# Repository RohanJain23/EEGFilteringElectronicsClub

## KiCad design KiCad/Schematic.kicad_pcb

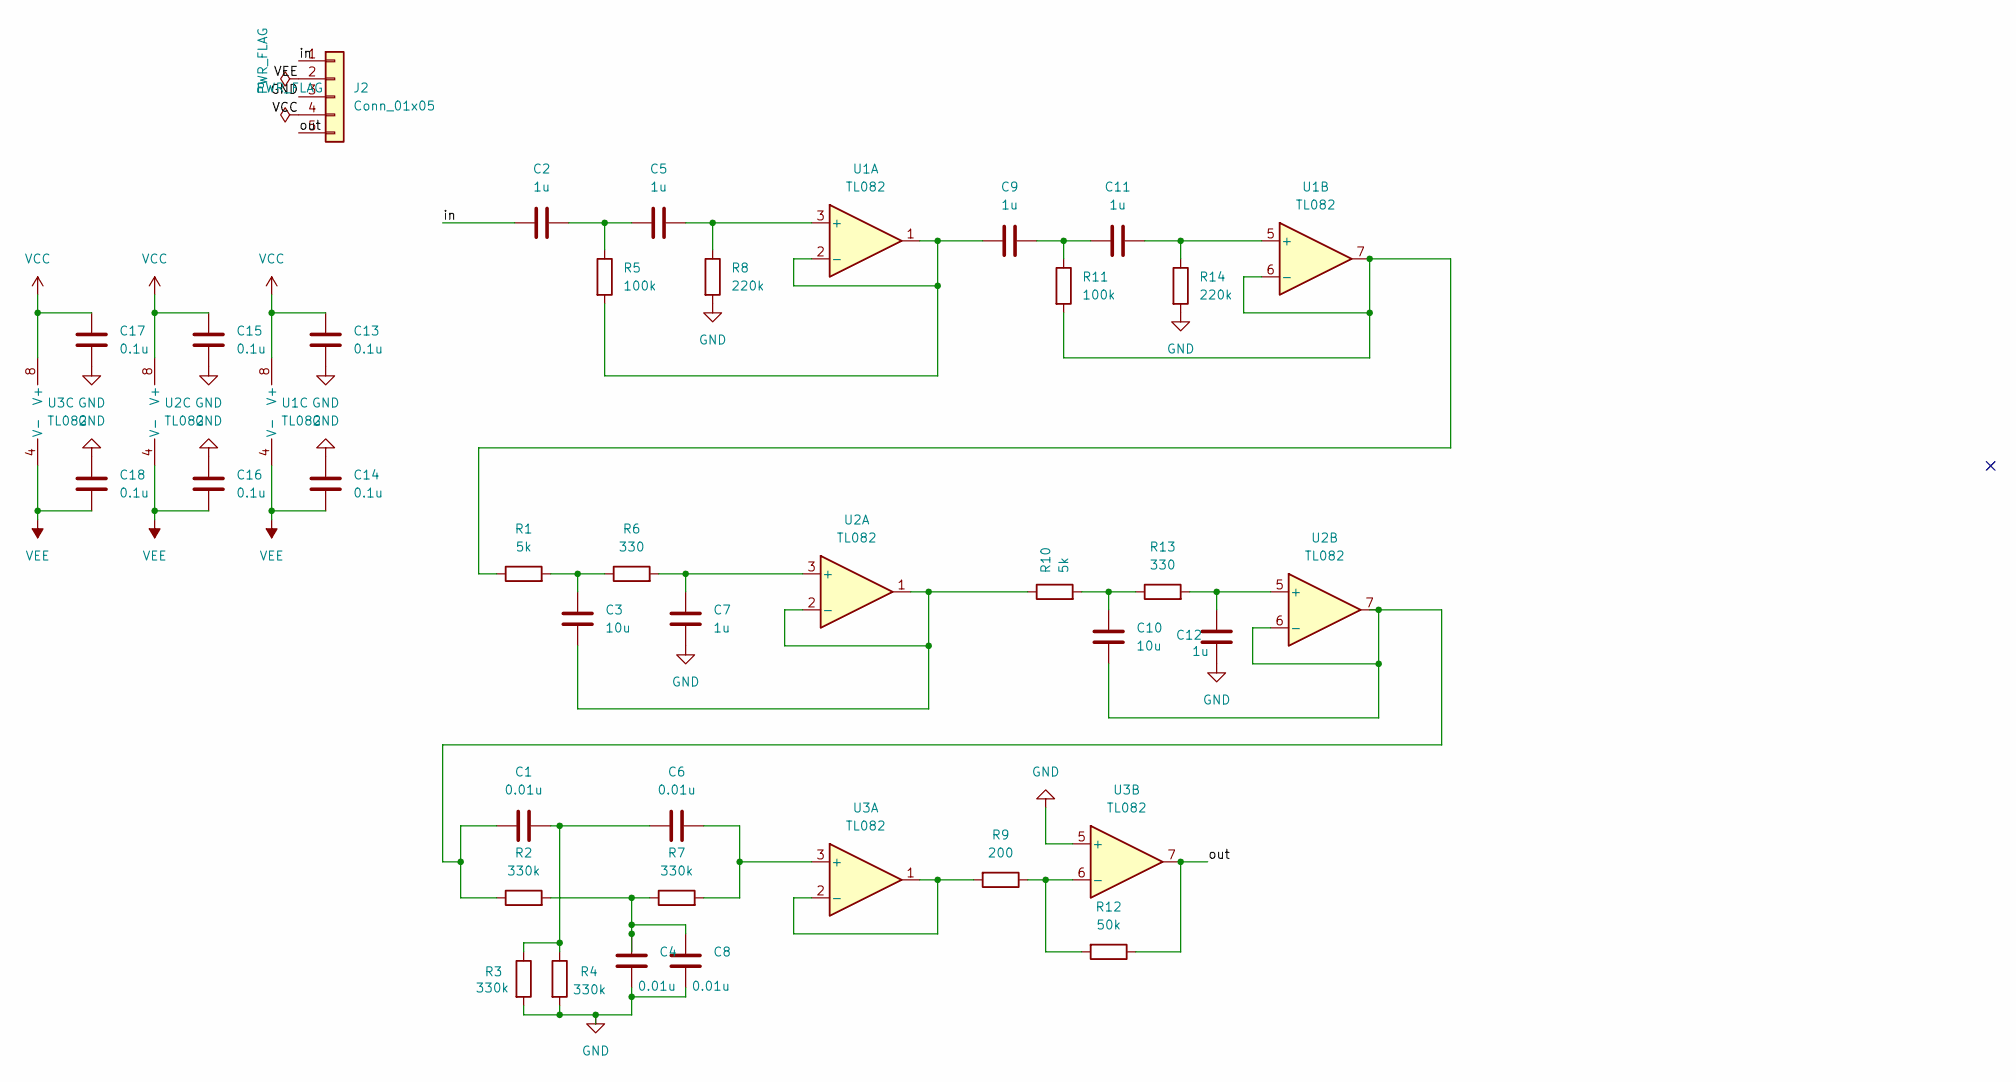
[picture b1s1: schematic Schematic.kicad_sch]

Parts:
C1, C4, C6, C8: 0.01u; C_Disc_D5.0mm_W2.5mm_P5.00mm
C2, C5, C7, C9, C11, C12: 1u; CP_Radial_D5.0mm_P2.50mm
C3, C10: 10u; CP_Radial_D5.0mm_P2.50mm
C13, C14, C15, C16, C17, C18: 0.1u; C_Disc_D5.0mm_W2.5mm_P5.00mm
J2: Conn_01x05; PinHeader_1x05_P2.54mm_Vertical
R1, R10: 5k; R_Axial_DIN0207_L6.3mm_D2.5mm_P7.62mm_Horizontal
R2, R3, R4, R7: 330k; R_Axial_DIN0207_L6.3mm_D2.5mm_P7.62mm_Horizontal
R5, R11: 100k; R_Axial_DIN0207_L6.3mm_D2.5mm_P7.62mm_Horizontal
R6, R13: 330; R_Axial_DIN0207_L6.3mm_D2.5mm_P7.62mm_Horizontal
R8, R14: 220k; R_Axial_DIN0207_L6.3mm_D2.5mm_P7.62mm_Horizontal
R9: 200; R_Axial_DIN0207_L6.3mm_D2.5mm_P7.62mm_Horizontal
R12: 50k; R_Axial_DIN0207_L6.3mm_D2.5mm_P7.62mm_Horizontal
U1, U2, U3: TL082; DIP-8_W7.62mm

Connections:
/in: C2.1, J2.1
/out: J2.5, R12.1, U3.7
GND: C4.2, C7.2, C8.2, C12.2, C13.2, C14.1, C15.2, C16.1, C17.2, C18.1, J2.3, R3.2, R4.2, R8.2, R14.2, U3.5 (+)
unnamed: C1.2, C6.1, R3.1, R4.1
unnamed: C2.2, C5.1, R5.1
unnamed: C3.1, R1.2, R6.1
unnamed: C4.1, C8.1, R2.2, R7.1
unnamed: C10.1, R10.2, R13.1
unnamed: C9.2, C11.1, R11.1
unnamed: C5.2, R8.1, U1.3 (+)
unnamed: C9.1, R5.2, U1.1, U1.2 (-)
unnamed: C11.2, R14.1, U1.5 (+)
unnamed: R1.1, R11.2, U1.6 (-), U1.7
unnamed: C7.1, R6.2, U2.3 (+)
unnamed: C3.2, R10.1, U2.1, U2.2 (-)
unnamed: C12.1, R13.2, U2.5 (+)
unnamed: C1.1, C10.2, R2.1, U2.6 (-), U2.7
unnamed: C6.2, R7.2, U3.3 (+)
unnamed: R9.2, U3.1, U3.2 (-)
unnamed: R9.1, R12.2, U3.6 (-)
VCC: C13.1, C15.1, C17.1, J2.4, U1.8 (V+), U2.8 (V+), U3.8 (V+)
VEE: C14.2, C16.2, C18.2, J2.2, U1.4 (V-), U2.4 (V-), U3.4 (V-)

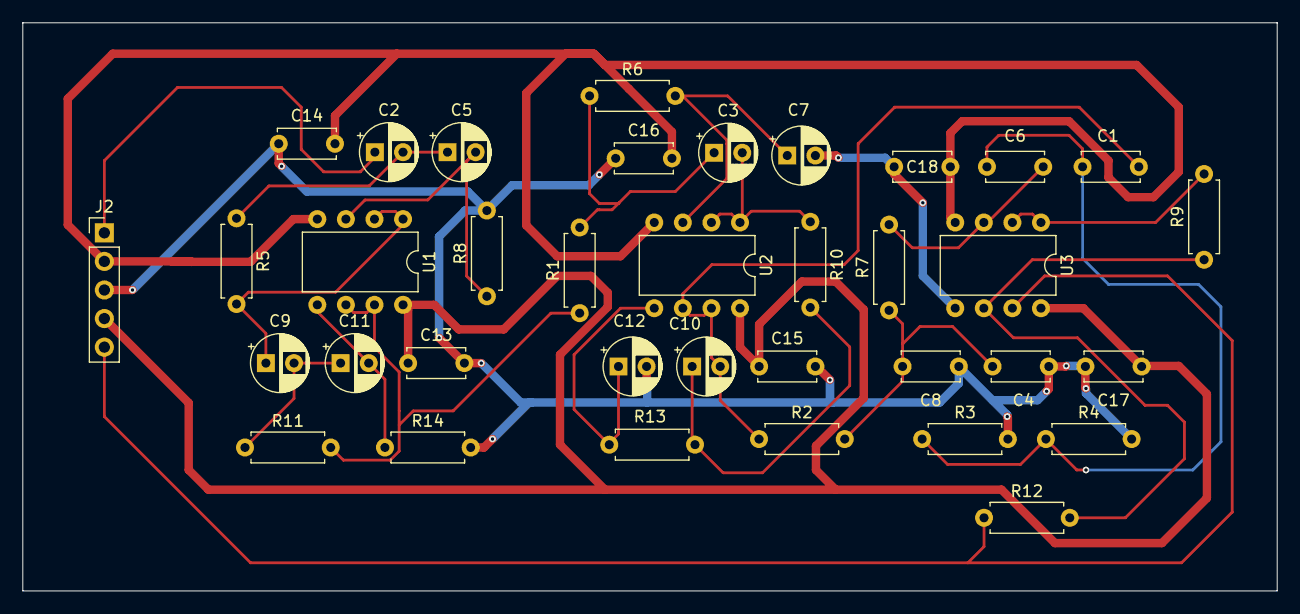
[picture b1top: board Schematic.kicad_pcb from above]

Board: 2 copper layers, 111.5 x 50.5 mm, 36 parts (0 on the bottom side), 22 nets.

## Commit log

2026-05-27 Create LTSpice
2026-05-27 Create Vivado DSP
2026-05-27 Create KiCad PCB
